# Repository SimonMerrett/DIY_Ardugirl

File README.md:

# DIY_Ardugirl
A SAMD21-based riff on the Arduboy handheld console. This is definitely Work in Progress and is not for production

The original has:
- ATmega32u4 processor 
- small OLED screen
- no additional storage
- speaker

This will have
- SAMD21G18A as it's processor
- larger daylight readable LCD screen, with dimmable backlight
- SPI flash and micro SD card slot (overkill - the latter may not be populated)
- headphone jack
- infrared rx/tx for possible multiplayer comms
- optional mini joystick

# Forum discussion
The Arduboy forum has [a thread](https://community.arduboy.com/t/wip-simon-merretts-arduboy-clone/6676) relevant to this design

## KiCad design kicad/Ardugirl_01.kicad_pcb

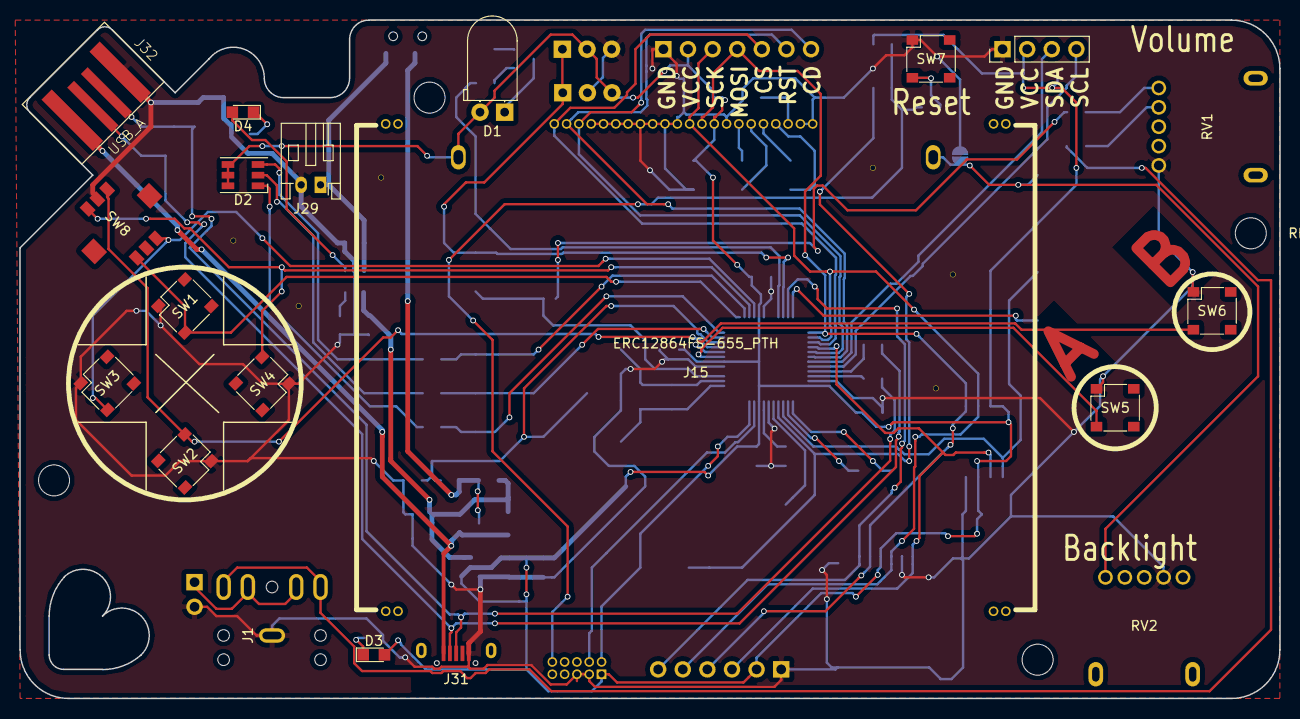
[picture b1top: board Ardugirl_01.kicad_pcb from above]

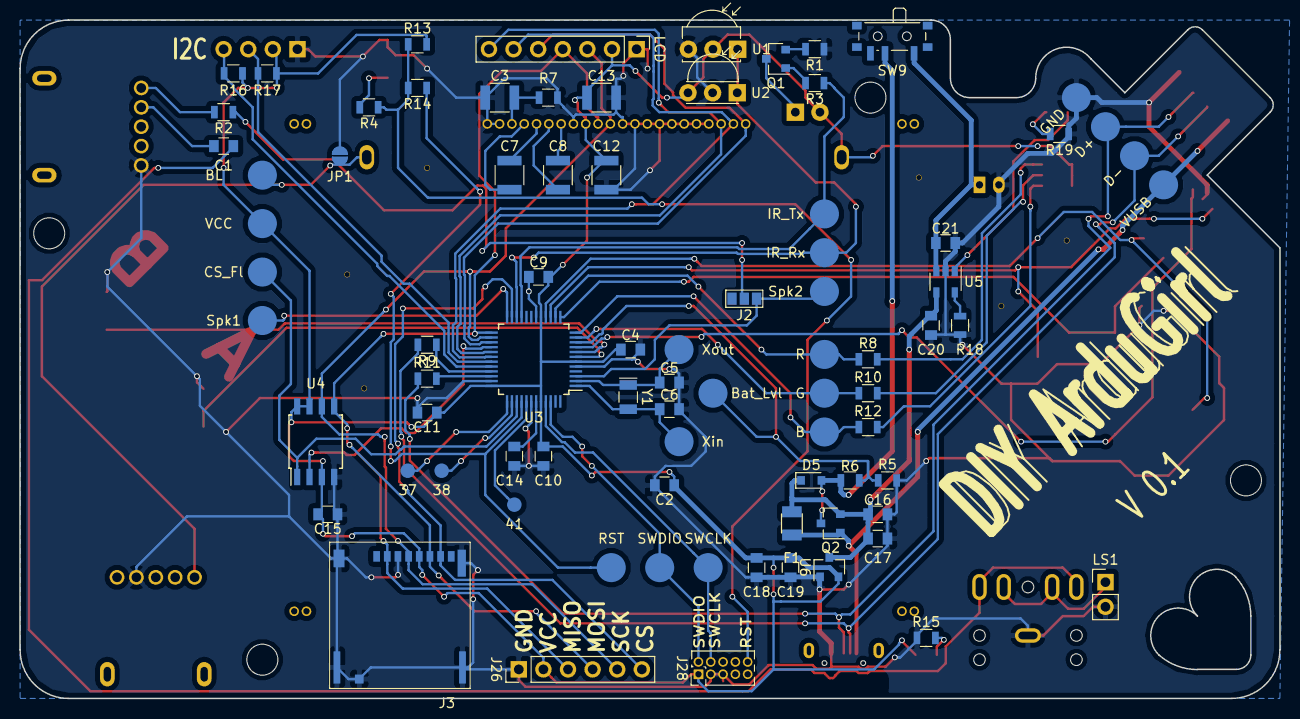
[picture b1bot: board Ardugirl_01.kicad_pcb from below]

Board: 2 copper layers, 130.0 x 70.0 mm, 102 parts (82 on the bottom side), 66 nets.

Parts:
37, 38: TP_Small; Measurement_Point_Round-SMD-Pad_Small
41: Measurement_Point_Round-SMD-Pad_Small
B: TEST; Measurement_Point_Round-SMD-Pad_Big
BL: K(-); Measurement_Point_Round-SMD-Pad_Big
Bat_Lvl: TEST; Measurement_Point_Round-SMD-Pad_Big
C1: 100u; C_0805
C2: 47u; C_0805
C3: 0.33u 25V; C_1210
C4, C9, C10, C11: 100n; C_0805
C5, C6: 12.5p; C_0805
C7, C8: 2.2u; C_1210
C12: 0.1u; C_1210
C13: 10u; C_1210
C14: C; C_0805
C15, C20, C21: 10u; C_0805
C16: Xu; C_0805
C17, C18: 1u; C_0805
C19: 0.1u; C_0805
CS_Fl: TEST; Measurement_Point_Round-SMD-Pad_Big
D1: IR_LED; LED_D5.0mm_Horizontal_O1.27mm_Z9.0mm
D2: LED_RGB; LED_RGB_PLCC-6
D3: PWR_LED; LED_0805
D4: LED; LED_0805
D5: D_Schottky; D_0805
D+: TEST; Measurement_Point_Round-SMD-Pad_Big
D-: TEST; Measurement_Point_Round-SMD-Pad_Big
F1: Polyfuse; Fuse_SMD1206_Reflow
G: TEST; Measurement_Point_Round-SMD-Pad_Big
GND: TEST_1P; Measurement_Point_Round-SMD-Pad_Big
I2C: I2C Header; Pin_Header_Straight_1x04_Pitch2.54mm
IR_Rx: TEST; Measurement_Point_Round-SMD-Pad_Big
IR_Tx: TEST; Measurement_Point_Round-SMD-Pad_Big
J1: JACK_TRS_5PINS; 3.5mm_Jack_5P
J2: GS3
J3: Micro_SD_Card; uSD_Molex
J15: CONN_01X24; ERC12864FS-655_PTH
J26: SD Header; Pin_Header_Straight_1x06_Pitch2.54mm
J28: SWD_02X05; Pin_Header_Straight_2x05_Pitch1.27mm
J29: CONN_BATT; JST_PH_S2B-PH-K_02x2.00mm_Angled
J31: USB_A; USB_micro-Korean_UF-M5DD-Y1
J32: USB_A; USB-A-PCB
JP1: Jumper_NO; JUMPER-SOLDER-SMD
LCD: LDC Header; Socket_Strip_Straight_1x07_Pitch2.54mm
LS1: Speaker; Pin_Header_Straight_1x02_Pitch2.54mm
Q1: Q_NMOS_GSD; SOT-23
Q2: Q_PMOS_GSD; SOT-23
R: TEST; Measurement_Point_Round-SMD-Pad_Big
R1: R; R_0805
R2: 270R; R_0805
R3, R9, R11: 22R; R_0805
R4: 47R; R_0805
R5, R6, R13, R16, R17: 10k; R_0805
R7: 10M; R_0805
R8, R10, R12, R15: 220R; R_0805
R14: 330R; R_0805
R18: 2k; R_0805
R19: 1k; R_0805
RST: TEST_1P; Measurement_Point_Round-SMD-Pad_Big
RV1: POT; Variable_R_PTH_5pin_14mm
RV2: 1k; Variable_R_PTH_5pin_14mm
SW1: UP; SW_Tactile_SMD_4.8_4.8
SW2: DOWN; SW_Tactile_SMD_4.8_4.8
SW3: LEFT; SW_Tactile_SMD_4.8_4.8
SW4: RIGHT; SW_Tactile_SMD_4.8_4.8
SW5: Button_A; SW_Tactile_SMD_4.8_4.8
SW6: Button_B; SW_Tactile_SMD_4.8_4.8
SW7: Reset; SW_Tactile_SMD_4.8_4.8
SW8: Joystick_5W; Joystick_5W_SKRH
SW9: SW_SPDT; SW_SPDT_PCM12
SWCLK: TEST; Measurement_Point_Round-SMD-Pad_Big
SWDIO: TEST; Measurement_Point_Round-SMD-Pad_Big
Spk1, Spk2: TEST; Measurement_Point_Round-SMD-Pad_Big
U1: TSOP325xx; IRReceiver_Vishay_MOLD-3pin
U2: TSOP335xx; IRReceiver_Vishay_MINIMOLD-3pin
U3: SAMD21G18A-MU; TQFP-48_7x7mm_Pitch0.5mm
U4: SST25PF040C; SOIJ-8_5.3x5.3mm_Pitch1.27mm
U5: MCP73831; SOT-23-5
U6: MCP1700T-3002E/TT; SOT-23
VCC: A(+); Measurement_Point_Round-SMD-Pad_Big
VUSB: TEST_1P; Measurement_Point_Round-SMD-Pad_Big
Xin: TEST; Measurement_Point_Round-SMD-Pad_Big
Xout: TEST; Measurement_Point_Round-SMD-Pad_Big
Y1: 32.768kHz; Crystal_SMD_G8-2pin_3.2x1.5mm

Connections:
/BL: BL.1, J15.24, JP1.1, RV2.3
/Batt_Level: Bat_Lvl.1, R5.1, R6.2, U3.10
/Button_A: SW5.2, U3.7
/Button_B: SW6.2, U3.8
/D+: D+.1, J31.3, J32.3, R11.1
/D-: D-.1, J31.2, J32.2, R9.2
/DOWN: SW2.2, SW8.4, U3.9
/Flash_CS: CS_Fl.1, U3.39, U4.1
/I2C_SCL: I2C.4, R16.1, U3.32
/I2C_SDA: I2C.3, R17.2, U3.31
/IR_Rx: IR_Rx.1, U1.1, U2.1, U3.22
/IR_Tx: IR_Tx.1, R3.1, U3.21
/LCD_CD: J15.3, LCD.7, U3.29
/LCD_CS: J15.1, LCD.5, U3.27
/LCD_RST: J15.2, LCD.6, U3.30
/LEFT: SW3.2, SW8.3, U3.16
/MISO: J3.7, J26.3, U3.28, U4.2
/MOSI: J3.3, J15.13, J26.4, LCD.4, U3.25, U4.5
/RESET: J28.10, R4.1, R13.1, R14.2
/RGB_Blue: B.1, R12.1, U3.12
/RGB_Green: G.1, R10.1, U3.11
/RGB_Red: R.1, R8.1, U3.14
/RIGHT: SW4.2, SW8.6, U3.15
/SCK: J3.5, J15.12, J26.5, LCD.3, U3.26, U4.6
/SD_CS: J3.2, J26.6, U3.23
/SWCLK: J28.4, SWCLK.1, U3.45
/SWDIO: J28.2, SWDIO.1, U3.46
/Sp+: J1.3, J1.4, LS1.1
/Speaker2: J2.3, Spk2.1, U3.3
/Speaker_1: Spk1.1, U3.24
/UP: SW1.2, SW8.1, U3.13
/VBAT: C21.1, J29.1, SW9.1, U5.3
/VCC: C2.1, C4.1, C9.2, C10.1, C11.1, C12.1, C13.1, C15.2, C18.1, C19.1, D1.2, D2.4, D2.5, D2.6, D3.2, I2C.2, J3.4, J15.14, J15.23, J26.2, J28.1, LCD.2, R13.2, R16.2, R17.1, U1.2, U2.3, U3.6, U3.17, U3.36, U3.44, U4.3, U4.7, U4.8, U6.2, VCC.1
/VIN: C16.1, C17.1, C20.1, D5.1, F1.1, Q2.2, U5.4, U6.3
/VSW: D5.2, Q2.3, R6.1, SW9.2
/VUSB: F1.2, J31.1, J32.1, Q2.1, VUSB.1
/Xtal_in: C6.1, U3.1, Xin.1, Y1.2
/Xtal_out: C5.1, U3.2, Xout.1, Y1.1
GND: C2.2, C3.1, C4.2, C5.2, C6.2, C9.1, C10.2, C11.2, C12.2, C13.2, C14.2, C15.1, C16.2, C17.2, C18.2, C19.2, C20.2, C21.2, GND.1, I2C.1, J1.1, J3.6, J3.9, J15.4, J15.5, J15.6, J15.7, J15.8, J15.9, J15.10, J15.11, J15.15, J15.21, J15.22, J26.1, J28.3, J28.5, J29.2, J31.4, J31.5, J32.4, JP1.2, LCD.1, LS1.2, R1.1, R5.2, R7.1, R15.1, R18.2, R19.1, RV1.3, RV2.2, SW1.1, SW2.1, SW3.1, SW4.1, SW5.1, SW6.1, SW7.1, SW8.5, U1.3, U2.2, U3.5, U3.18, U3.35, U3.42, U4.4, U5.2, U6.1
unnamed: C1.1, RV1.2
unnamed: C1.2, J1.2, J1.5
unnamed: C3.2, J15.20, R7.2
unnamed: C7.1, J15.19
unnamed: C7.2, J15.18
unnamed: C8.1, J15.17
unnamed: C8.2, J15.16
unnamed: C14.1, U3.43
unnamed: D1.1, Q1.3
unnamed: D2.1, R12.2
unnamed: D2.2, R10.2
unnamed: D2.3, R8.2
unnamed: D3.1, R15.2
unnamed: D4.1, R19.2
unnamed: D4.2, U5.1
unnamed: J2.2, R2.1
unnamed: R14.1, RST.1, U3.40
unnamed: Q1.1, R3.2
unnamed: Q1.2, R1.2
unnamed: R2.2, RV1.1
unnamed: R4.2, SW7.2
unnamed: R9.1, U3.33
unnamed: R11.2, U3.34
unnamed: R18.1, U5.5
unnamed: 37.1, U3.37
unnamed: 38.1, U3.38
unnamed: 41.1, U3.41

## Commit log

2019-01-01 Update README.md
    Added more detail and corrected typo
2019-01-01 First upload of V0.1 files for collaboration
2019-01-01 Delete first.txt
    Was only required to create folder structure
2019-01-01 Update README.md
    Added forum link
